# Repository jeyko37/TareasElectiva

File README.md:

# Tareas Diseño Mecatronico
Mi pecadora - Omega

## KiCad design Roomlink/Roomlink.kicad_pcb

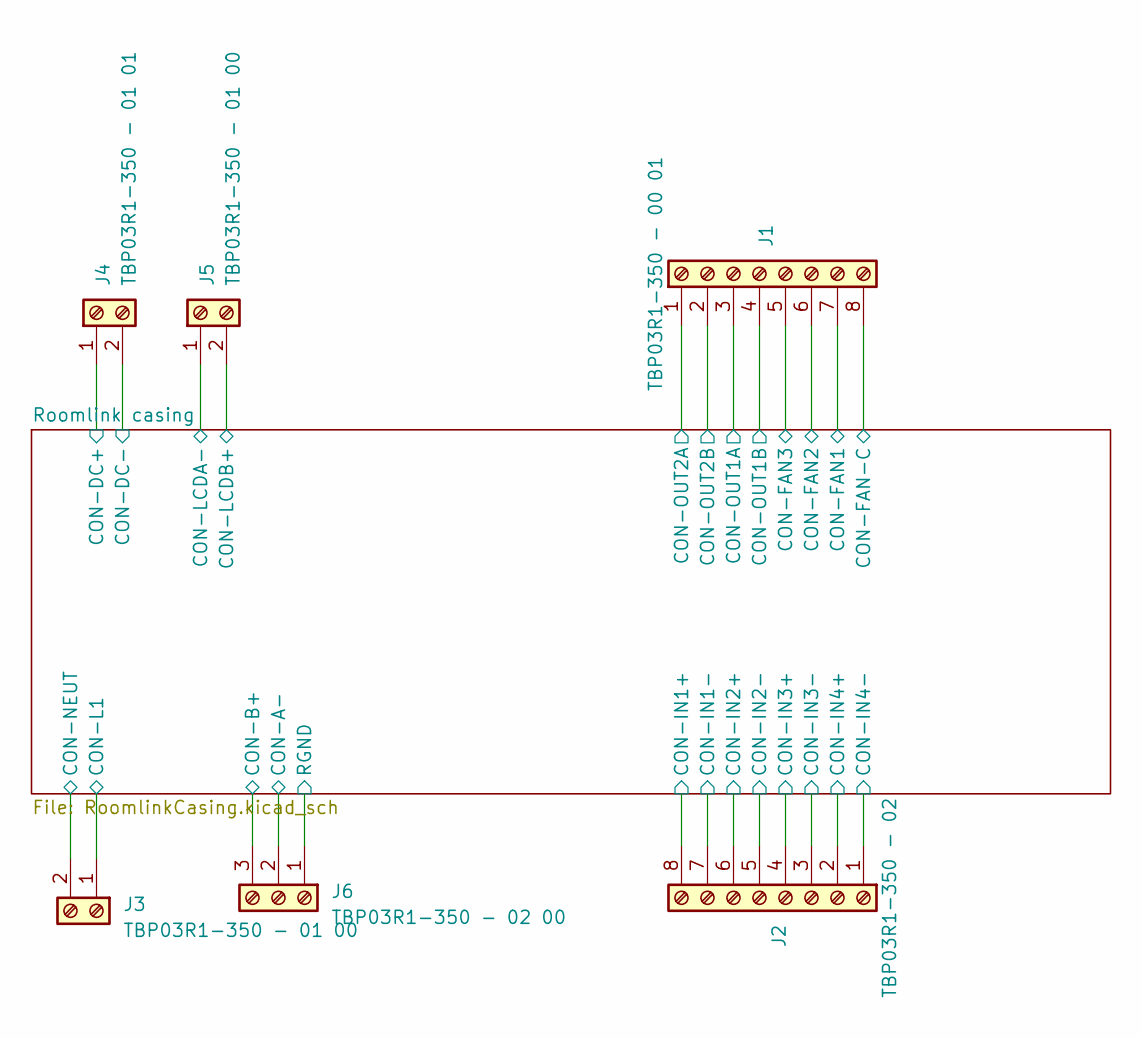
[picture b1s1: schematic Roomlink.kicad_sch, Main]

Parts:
J1: Screw_Terminal_01x08; CUI_TBP03R1-350-08GR; Part No. TBP03R1-350 - 00 01
J2: Screw_Terminal_01x08; CUI_TBP03R1-350-08GR; Part No. TBP03R1-350 - 02
J3, J5: TBP03R1-350 - 01 00; CUI_TBP03R1-350-02GR
J4: TBP03R1-350 - 01 01; CUI_TBP03R1-350-02GR
J6: TBP03R1-350 - 02 00; CUI_TBP03R1-350-03GR

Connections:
/Roomlink casing/CON-B+: J6.3; also elsewhere on the board
/Roomlink casing/CON-FAN1: J1.7; also elsewhere on the board
/Roomlink casing/CON-FAN2: J1.6; also elsewhere on the board
/Roomlink casing/CON-FAN3: J1.5; also elsewhere on the board
/Roomlink casing/CON-FAN-C: J1.8; also elsewhere on the board
/Roomlink casing/CON-IN1+: J2.8; also elsewhere on the board
/Roomlink casing/CON-IN1-: J2.7; also elsewhere on the board
/Roomlink casing/CON-IN2+: J2.6; also elsewhere on the board
/Roomlink casing/CON-IN2-: J2.5; also elsewhere on the board
/Roomlink casing/CON-IN3+: J2.4; also elsewhere on the board
/Roomlink casing/CON-IN3-: J2.3; also elsewhere on the board
/Roomlink casing/CON-IN4+: J2.2; also elsewhere on the board
/Roomlink casing/CON-IN4-: J2.1; also elsewhere on the board
/Roomlink casing/CON-L1: J3.1; also elsewhere on the board
/Roomlink casing/CON-LCDA-: J5.1; also elsewhere on the board
/Roomlink casing/CON-LCDB+: J5.2; also elsewhere on the board
/Roomlink casing/CON-NEUT: J3.2; also elsewhere on the board
/Roomlink casing/CON-OUT1A: J1.3; also elsewhere on the board
/Roomlink casing/CON-OUT1B: J1.4; also elsewhere on the board
/Roomlink casing/CON-OUT2A: J1.1; also elsewhere on the board
/Roomlink casing/CON-OUT2B: J1.2; also elsewhere on the board
/Roomlink casing/RGND: J6.1; also elsewhere on the board

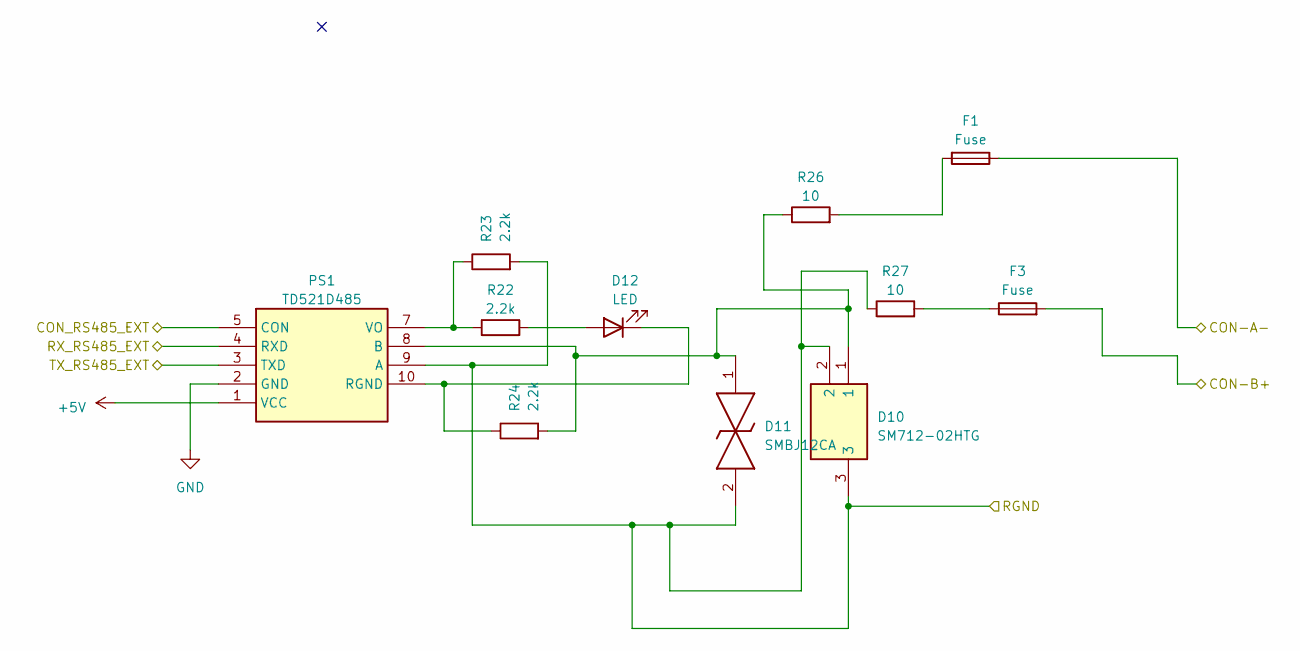
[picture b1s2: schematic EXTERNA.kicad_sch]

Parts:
D10: SM712-02HTG; SM71202HTG; Manufacturer_Part_Number SM712-02HTG; Mouser Part Number 576-SM712-02HTG
D11: SMBJ12CA; DIONM5436X245N; Manufacturer_Part_Number SMBJ12CA; Mouser Part Number 821-SMBJ12CA
D12: LED; LED_0805_2012Metric_Pad1.15x1.40mm_HandSolder
F1, F3: Fuse; Fuse_0805_2012Metric
PS1: TD521D485; Manufacturer_Part_Number TD521D485
R22, R23, R24: 2.2k; R_0805_2012Metric_Pad1.20x1.40mm_HandSolder
R26, R27: 10; R_0805_2012Metric_Pad1.20x1.40mm_HandSolder

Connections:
+5V: PS1.1 (VCC); also elsewhere on the board
/Roomlink casing/CON-B+: F3.2; also elsewhere on the board
/Roomlink casing/CONTROL/CON_RS485_EXT: PS1.5 (CON); also elsewhere on the board
/Roomlink casing/CONTROL/RX_RS485_EXT: PS1.4 (RXD); also elsewhere on the board
/Roomlink casing/CONTROL/TX_RS485_EXT: PS1.3 (TXD); also elsewhere on the board
/Roomlink casing/RGND: D10.2, D10.3, D11.2, PS1.9 (A), R23.2, R27.1; also elsewhere on the board
unnamed: D12.2 (A), R22.2
unnamed: D12.1 (K), PS1.10 (RGND), R24.1
unnamed: F3.1, R27.2
unnamed: D10.1, D11.1, PS1.8 (B), R24.2, R26.1
unnamed: PS1.7 (VO), R22.1, R23.1

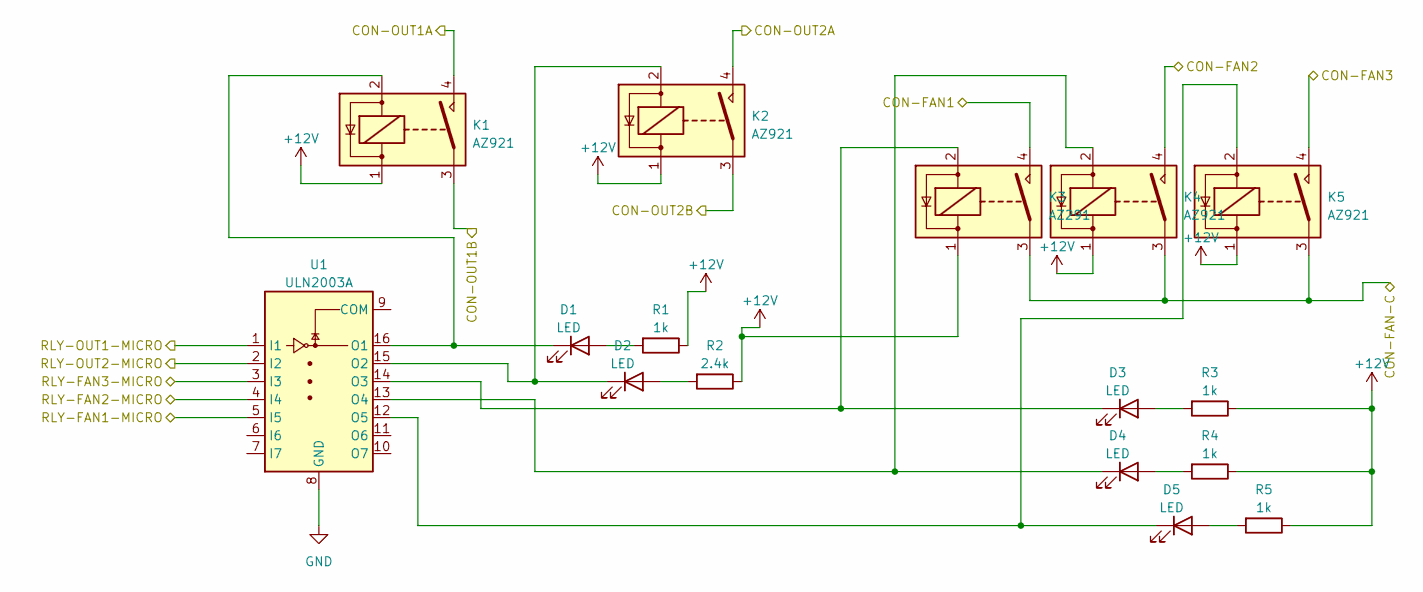
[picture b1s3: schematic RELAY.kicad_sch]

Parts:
D1, D2, D3, D4, D5: LED; LED_0805_2012Metric_Pad1.15x1.40mm_HandSolder
K1, K2, K4, K5: AZ921
K3: AZ291; AZ921
R1, R3, R4, R5: 1k; R_0805_2012Metric_Pad1.20x1.40mm_HandSolder
R2: 2.4k; R_0805_2012Metric_Pad1.20x1.40mm_HandSolder
U1: ULN2003A; DIP762W55P254L1940H508Q16N

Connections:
/Roomlink casing/CON-FAN1: K3.4; also elsewhere on the board
/Roomlink casing/CON-FAN2: K4.4; also elsewhere on the board
/Roomlink casing/CON-FAN3: K5.4; also elsewhere on the board
/Roomlink casing/CON-FAN-C: K3.3, K4.3, K5.3; also elsewhere on the board
/Roomlink casing/CON-OUT1A: K1.4; also elsewhere on the board
/Roomlink casing/CON-OUT1B: K1.3; also elsewhere on the board
/Roomlink casing/CON-OUT2A: K2.4; also elsewhere on the board
/Roomlink casing/CON-OUT2B: K2.3; also elsewhere on the board
/Roomlink casing/CONTROL/RLY-FAN1-MICRO: U1.5 (I5); also elsewhere on the board
/Roomlink casing/CONTROL/RLY-FAN2-MICRO: U1.4 (I4); also elsewhere on the board
/Roomlink casing/CONTROL/RLY-FAN3-MICRO: U1.3 (I3); also elsewhere on the board
/Roomlink casing/CONTROL/RLY-OUT1-MICRO: U1.1 (I1); also elsewhere on the board
/Roomlink casing/CONTROL/RLY-OUT2-MICRO: U1.2 (I2); also elsewhere on the board
unnamed: D1.2 (A), R1.2
unnamed: D1.1 (K), K1.2, U1.16 (O1)
unnamed: D2.2 (A), R2.2
unnamed: D2.1 (K), K2.2, U1.15 (O2)
unnamed: D3.2 (A), R3.2
unnamed: D3.1 (K), K3.2, U1.14 (O3)
unnamed: D4.2 (A), R4.2
unnamed: D4.1 (K), K4.2, U1.13 (O4)
unnamed: D5.2 (A), R5.2
unnamed: D5.1 (K), K5.2, U1.12 (O5)

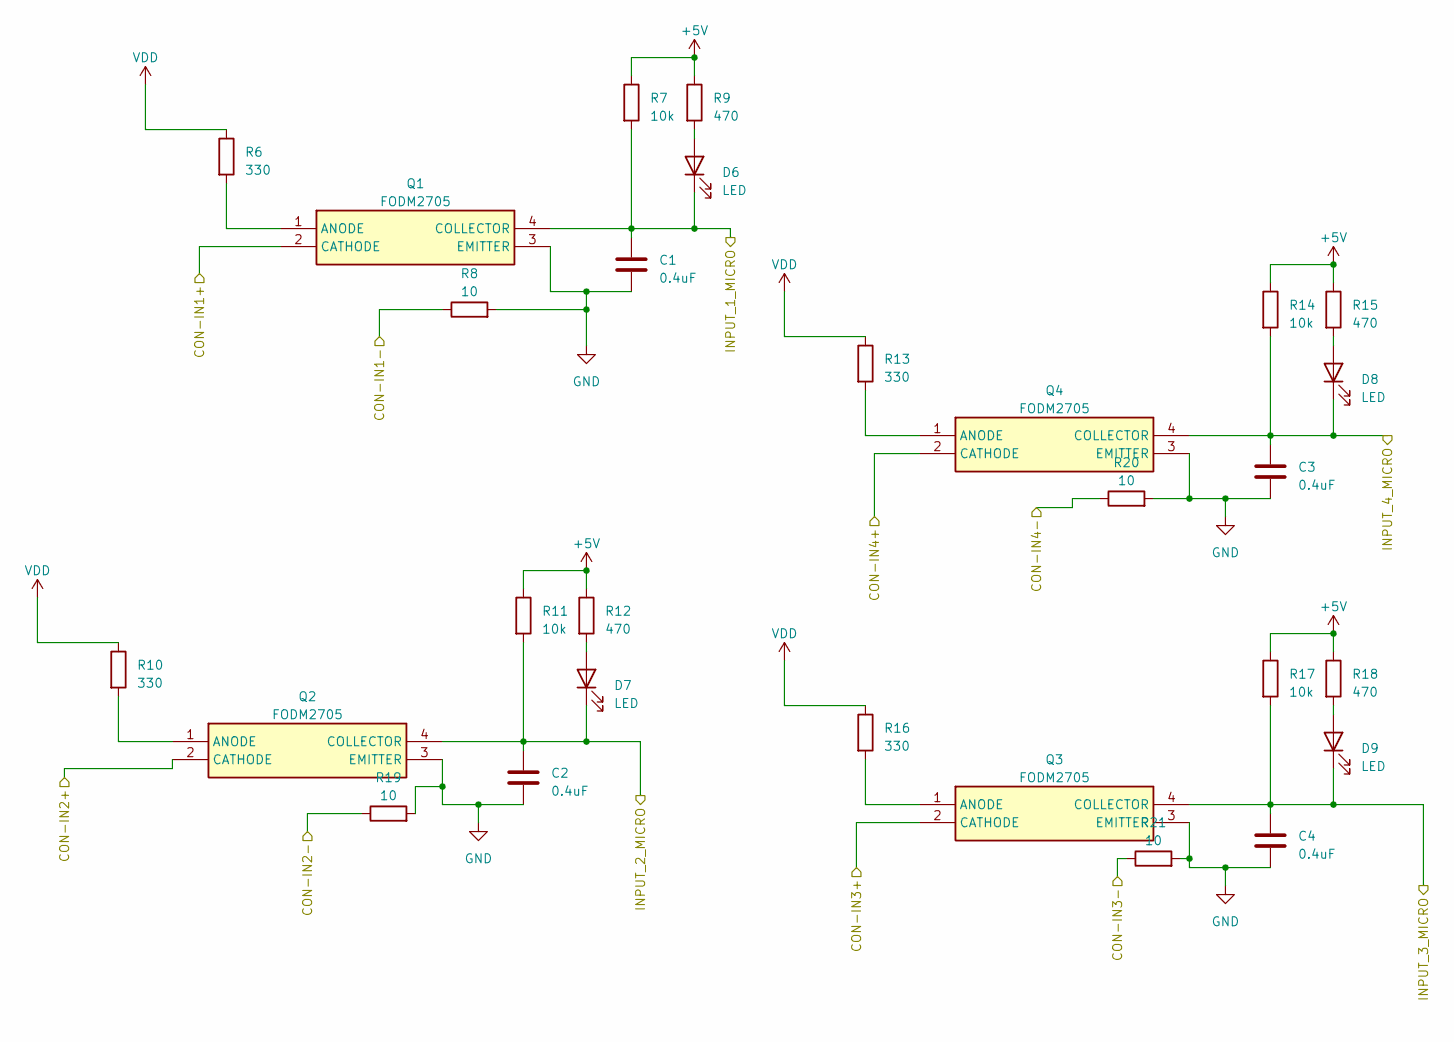
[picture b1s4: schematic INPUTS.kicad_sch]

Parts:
C1, C2, C3, C4: 0.4uF; C_0805_2012Metric_Pad1.18x1.45mm_HandSolder
D6, D7, D8, D9: LED; LED_0805_2012Metric_Pad1.15x1.40mm_HandSolder
Q1, Q2, Q3, Q4: FODM2705; SOP254P675X240-4N; Mouser Part Number 512-FODM2705
R6, R10, R13, R16: 330; R_0805_2012Metric_Pad1.20x1.40mm_HandSolder
R7, R11, R14, R17: 10k; R_0805_2012Metric_Pad1.20x1.40mm_HandSolder
R8, R19, R20, R21: 10; R_0805_2012Metric_Pad1.20x1.40mm_HandSolder
R9, R12, R15, R18: 470; R_0805_2012Metric_Pad1.20x1.40mm_HandSolder

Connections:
+5V: R7.1, R9.1, R11.1, R12.1, R14.1, R15.1, R17.1, R18.1; also elsewhere on the board
/Roomlink casing/CON-IN1+: Q1.2 (CATHODE); also elsewhere on the board
/Roomlink casing/CON-IN1-: R8.1; also elsewhere on the board
/Roomlink casing/CON-IN2+: Q2.2 (CATHODE); also elsewhere on the board
/Roomlink casing/CON-IN2-: R19.1; also elsewhere on the board
/Roomlink casing/CON-IN3+: Q3.2 (CATHODE); also elsewhere on the board
/Roomlink casing/CON-IN3-: R21.1; also elsewhere on the board
/Roomlink casing/CON-IN4+: Q4.2 (CATHODE); also elsewhere on the board
/Roomlink casing/CON-IN4-: R20.1; also elsewhere on the board
/Roomlink casing/CONTROL/INPUT_1_MICRO: C1.1, D6.1 (K), Q1.4 (COLLECTOR), R7.2; also elsewhere on the board
/Roomlink casing/CONTROL/INPUT_2_MICRO: C2.1, D7.1 (K), Q2.4 (COLLECTOR), R11.2; also elsewhere on the board
/Roomlink casing/CONTROL/INPUT_3_MICRO: C4.1, D9.1 (K), Q3.4 (COLLECTOR), R17.2; also elsewhere on the board
/Roomlink casing/CONTROL/INPUT_4_MICRO: C3.1, D8.1 (K), Q4.4 (COLLECTOR), R14.2; also elsewhere on the board
unnamed: D6.2 (A), R9.2
unnamed: D7.2 (A), R12.2
unnamed: D8.2 (A), R15.2
unnamed: D9.2 (A), R18.2
unnamed: Q1.1 (ANODE), R6.2
unnamed: Q2.1 (ANODE), R10.2
unnamed: Q3.1 (ANODE), R16.2
unnamed: Q4.1 (ANODE), R13.2
VDD: R6.1, R10.1, R13.1, R16.1; also elsewhere on the board

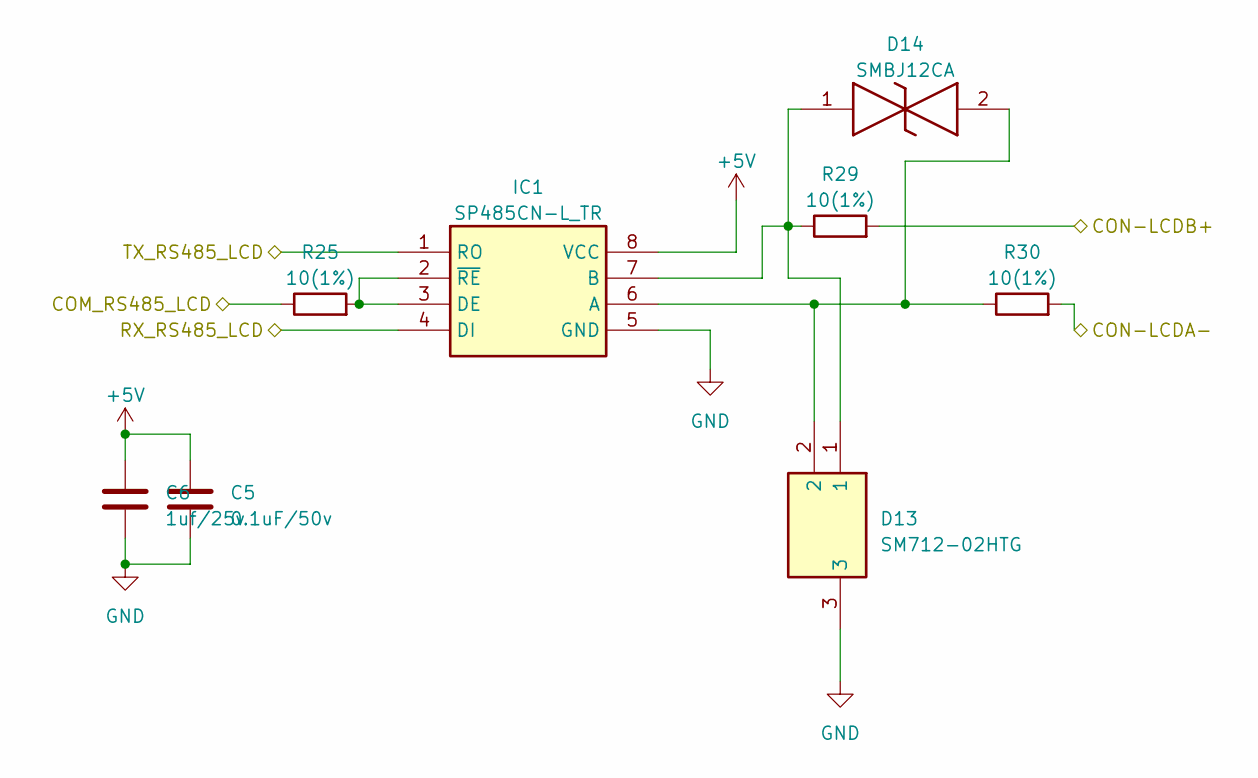
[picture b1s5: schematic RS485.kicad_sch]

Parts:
C5: 0.1uF/50v; C_0805_2012Metric_Pad1.18x1.45mm_HandSolder
C6: 1uf/25v; C_0805_2012Metric_Pad1.18x1.45mm_HandSolder
D13: SM712-02HTG; SM71202HTG; Manufacturer_Part_Number SM712-02HTG; Mouser Part Number 576-SM712-02HTG
D14: SMBJ12CA; DIONM5436X245N; Manufacturer_Part_Number SMBJ12CA; Mouser Part Number 821-SMBJ12CA
IC1: SP485CN-L_TR; SOIC127P600X175-8N; Manufacturer_Part_Number SP485CN-L/TR; Mouser Part Number 701-SP485CN-L/TR
R25, R29, R30: 10(1%); R_0805_2012Metric_Pad1.20x1.40mm_HandSolder

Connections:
+5V: C5.1, C6.1, IC1.8 (VCC); also elsewhere on the board
/Roomlink casing/CON-LCDA-: R30.2; also elsewhere on the board
/Roomlink casing/CON-LCDB+: R29.2; also elsewhere on the board
/Roomlink casing/CONTROL/COM_RS485_LCD: R25.1; also elsewhere on the board
/Roomlink casing/CONTROL/RX_RS485_LCD: IC1.4 (DI); also elsewhere on the board
/Roomlink casing/CONTROL/TX_RS485_LCD: IC1.1 (RO); also elsewhere on the board
unnamed: D13.2, D14.2, IC1.6 (A), R30.1
unnamed: D13.1, D14.1, IC1.7 (B), R29.1
unnamed: IC1.2 (~RE), IC1.3 (DE), R25.2

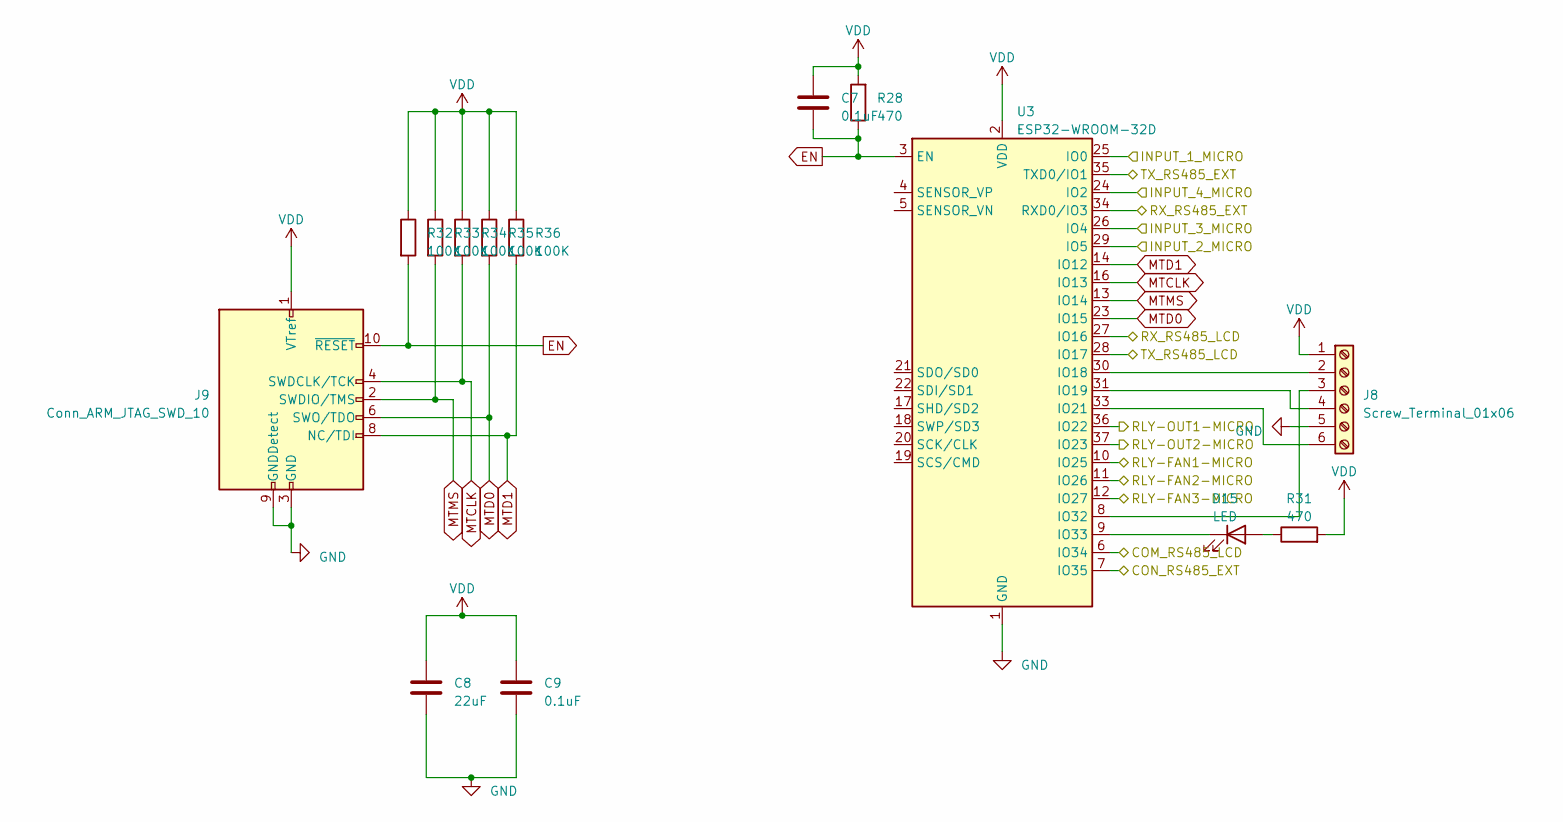
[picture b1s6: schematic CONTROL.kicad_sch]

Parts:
C7, C9: 0.1uF; C_0805_2012Metric_Pad1.18x1.45mm_HandSolder
C8: 22uF; C_0805_2012Metric_Pad1.18x1.45mm_HandSolder
D15: LED; LED_0805_2012Metric_Pad1.15x1.40mm_HandSolder
J8: Screw_Terminal_01x06; PinHeader_2x03_P2.54mm_Vertical
J9: Conn_ARM_JTAG_SWD_10; PinHeader_2x05_P2.54mm_Vertical
R28, R31: 470; R_0805_2012Metric_Pad1.20x1.40mm_HandSolder
R32, R33, R34, R35, R36: 100K; R_0805_2012Metric_Pad1.20x1.40mm_HandSolder
U3: ESP32-WROOM-32D

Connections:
/Roomlink casing/CONTROL/COM_RS485_LCD: U3.6 (IO34); also elsewhere on the board
/Roomlink casing/CONTROL/CON_RS485_EXT: U3.7 (IO35); also elsewhere on the board
/Roomlink casing/CONTROL/INPUT_1_MICRO: U3.25 (IO0); also elsewhere on the board
/Roomlink casing/CONTROL/INPUT_2_MICRO: U3.29 (IO5); also elsewhere on the board
/Roomlink casing/CONTROL/INPUT_3_MICRO: U3.26 (IO4); also elsewhere on the board
/Roomlink casing/CONTROL/INPUT_4_MICRO: U3.24 (IO2); also elsewhere on the board
/Roomlink casing/CONTROL/RLY-FAN1-MICRO: U3.10 (IO25); also elsewhere on the board
/Roomlink casing/CONTROL/RLY-FAN2-MICRO: U3.11 (IO26); also elsewhere on the board
/Roomlink casing/CONTROL/RLY-FAN3-MICRO: U3.12 (IO27); also elsewhere on the board
/Roomlink casing/CONTROL/RLY-OUT1-MICRO: U3.36 (IO22); also elsewhere on the board
/Roomlink casing/CONTROL/RLY-OUT2-MICRO: U3.37 (IO23); also elsewhere on the board
/Roomlink casing/CONTROL/RX_RS485_EXT: U3.34 (RXD0/IO3); also elsewhere on the board
/Roomlink casing/CONTROL/RX_RS485_LCD: U3.27 (IO16); also elsewhere on the board
/Roomlink casing/CONTROL/TX_RS485_EXT: U3.35 (TXD0/IO1); also elsewhere on the board
/Roomlink casing/CONTROL/TX_RS485_LCD: U3.28 (IO17); also elsewhere on the board
EN: C7.2, J9.10 (~RESET), R28.1, R32.2, U3.3 (EN)
MTCLK: J9.4 (SWDCLK/TCK), R34.2, U3.16 (IO13)
MTD0: J9.6 (SWO/TDO), R35.2, U3.23 (IO15)
MTD1: J9.8 (NC/TDI), R36.2, U3.14 (IO12)
MTMS: J9.2 (SWDIO/TMS), R33.2, U3.13 (IO14)
unnamed: D15.2 (A), R31.1
unnamed: D15.1 (K), U3.9 (IO33)
unnamed: J8.2, U3.30 (IO18)
unnamed: J8.3, U3.8 (IO32)
unnamed: J8.4, U3.31 (IO19)
unnamed: J8.6, U3.33 (IO21)
VDD: C7.1, C8.1, C9.1, J8.1, J9.1 (VTref), R28.2, R31.2, R32.1, R33.1, R34.1, R35.1, R36.1, U3.2 (VDD); also elsewhere on the board

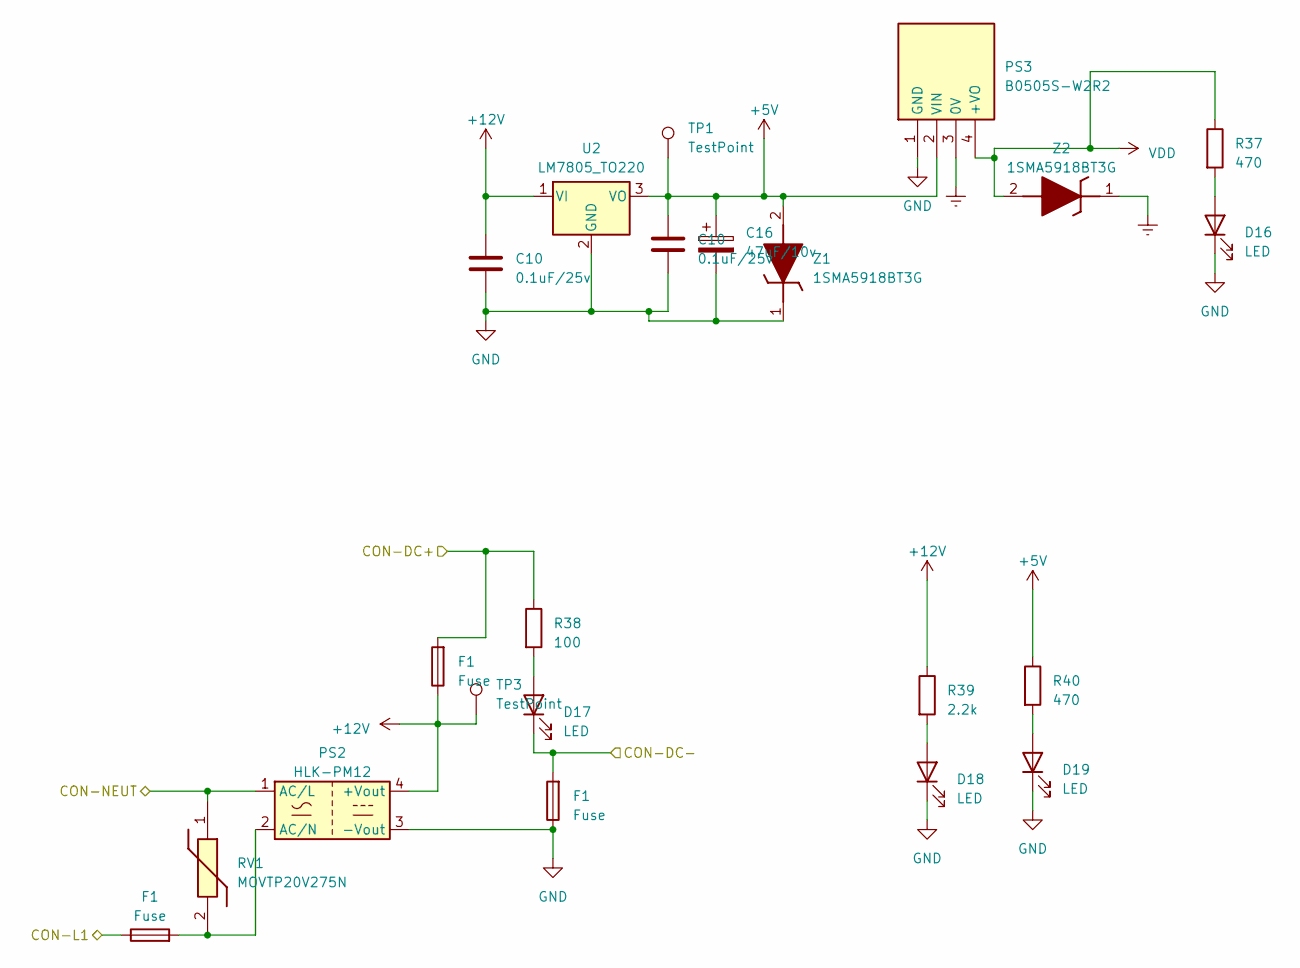
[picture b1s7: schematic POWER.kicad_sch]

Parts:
C10: 0.1uF/25v; C_0805_2012Metric_Pad1.18x1.45mm_HandSolder
C16: 47uF/10v; C_0805_2012Metric_Pad1.18x1.45mm_HandSolder
D16, D17, D18, D19: LED; LED_0805_2012Metric_Pad1.15x1.40mm_HandSolder
F1: Fuse; Fuse_0805_2012Metric
PS2: HLK-PM12; Converter_ACDC_HiLink_HLK-PMxx
PS3: B0505S-W2R2; B0505SW2R2; Manufacturer_Part_Number B0505S-W2R2
R37, R40: 470; R_0805_2012Metric_Pad1.20x1.40mm_HandSolder
R38: 100; R_0805_2012Metric_Pad1.20x1.40mm_HandSolder
R39: 2.2k; R_0805_2012Metric_Pad1.20x1.40mm_HandSolder
RV1: MOVTP20V275N; Manufacturer_Part_Number MOVTP20V275N
TP1, TP3: TestPoint; TestPoint_Pad_D1.5mm
U2: LM7805_TO220; TO-220-3_Vertical
Z1, Z2: 1SMA5918BT3G; DIOM5226X220N; Manufacturer_Part_Number 1SMA5918BT3G; Mouser Part Number 863-1SMA5918BT3G

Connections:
+5V: C16.1, PS3.2 (VIN), R40.1, TP1.1, U2.3 (VO), Z1.2 (A); also elsewhere on the board
/Roomlink casing/CON-NEUT: PS2.1 (AC/L), RV1.1; also elsewhere on the board
Earth: PS3.3 (0V), Z2.1 (K)
unnamed: D16.2 (A), R37.2
unnamed: D17.2 (A), R38.2
unnamed: D18.2 (A), R39.2
unnamed: D19.2 (A), R40.2
VDD: PS3.4 (+VO), R37.1, Z2.2 (A); also elsewhere on the board

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
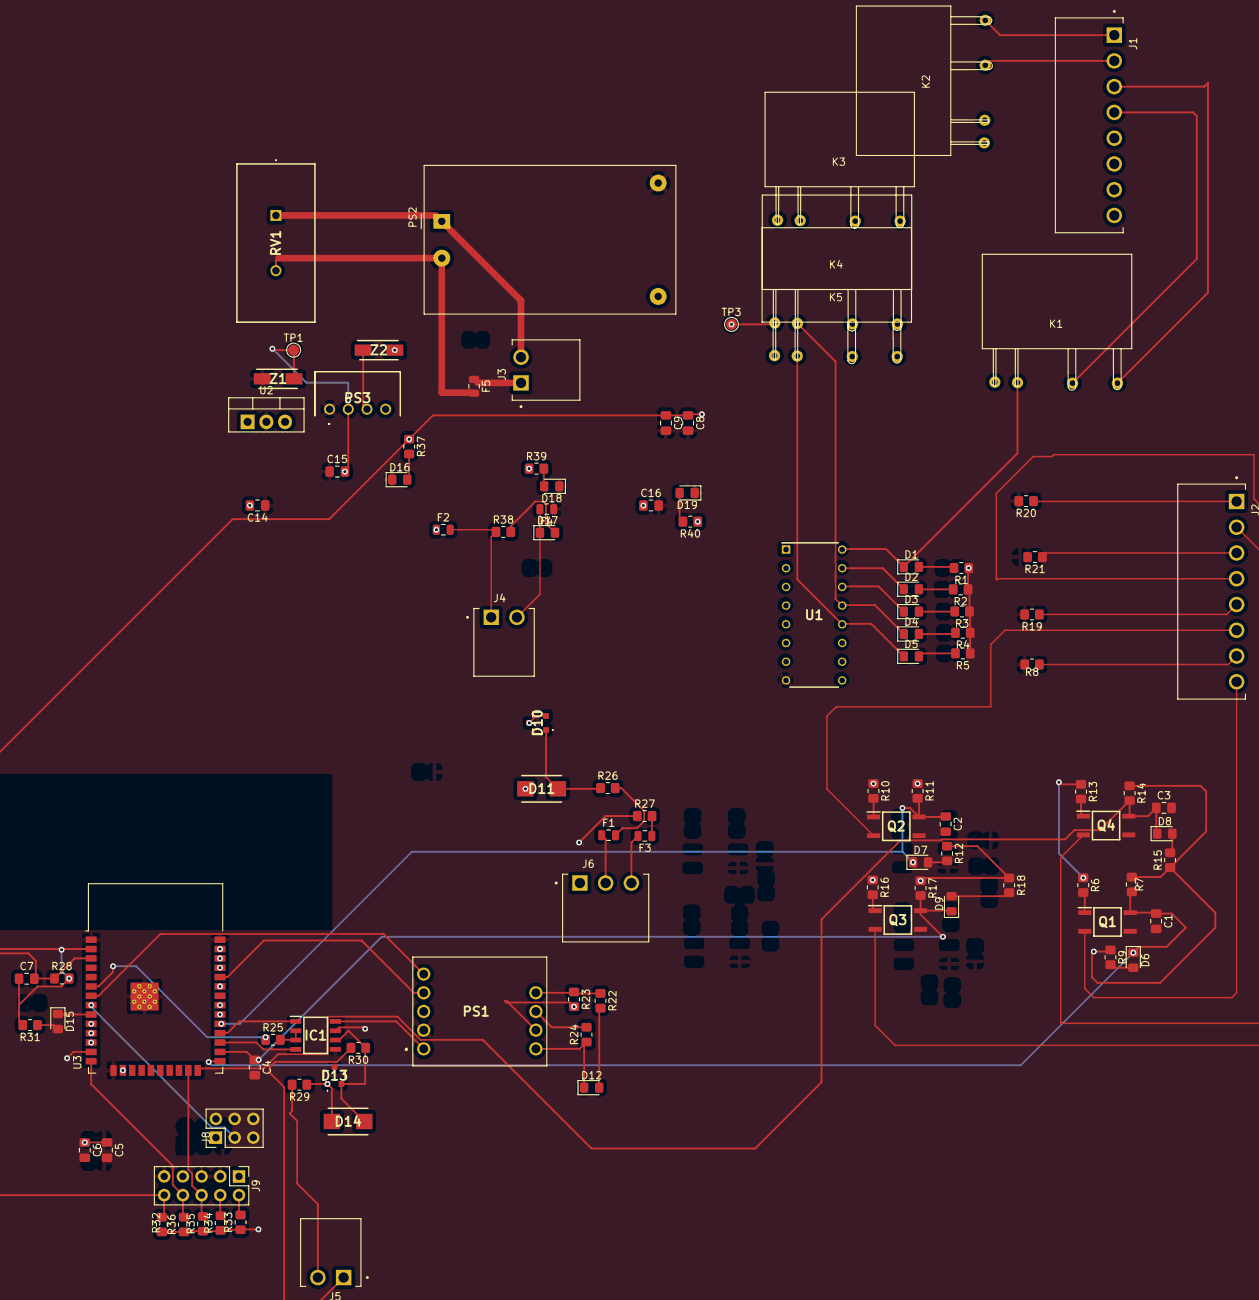
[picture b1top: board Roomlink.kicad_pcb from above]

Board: 8 copper layers, 105 parts (0 on the bottom side), 88 nets.

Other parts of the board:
C14, C15: 0.1uF/25v; C_0805_2012Metric_Pad1.18x1.45mm_HandSolder
F2, F4, F5: Fuse; Fuse_0805_2012Metric

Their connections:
+5V: C15.2; also elsewhere on the board
/Roomlink casing/CON-L1: F5.1; also elsewhere on the board

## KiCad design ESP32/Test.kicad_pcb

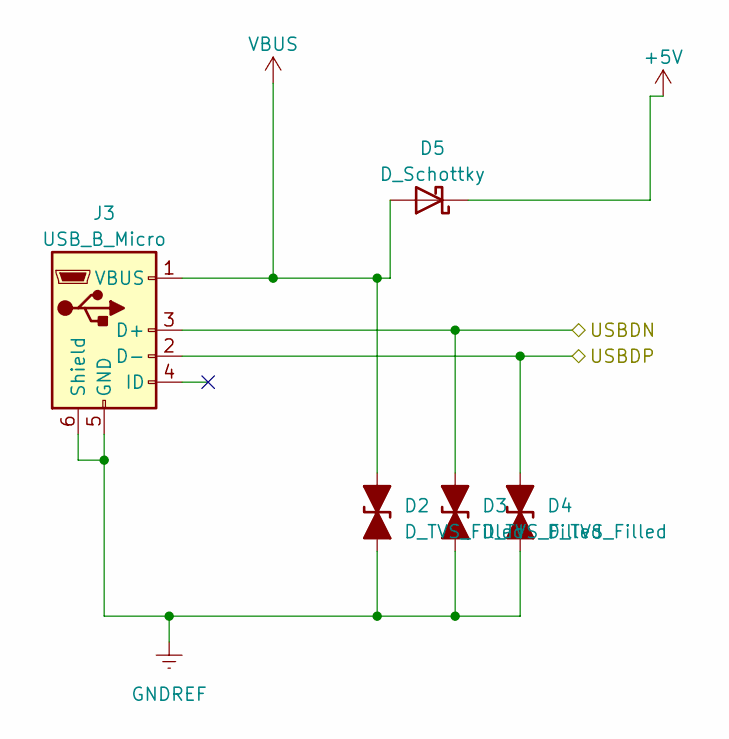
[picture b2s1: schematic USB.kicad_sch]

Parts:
D2, D3, D4: D_TVS_Filled; TVS_LESD5D5.0CT1G
D5: D_Schottky; D_SOD-323
J3: USB_B_Micro; USB_Micro-B_Molex-105017-0001

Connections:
+5V: D5.1 (K); also elsewhere on the board
/Micro_bus/USB_DN: D3.1 (A1), J3.3 (D+); also elsewhere on the board
/Micro_bus/USB_DP: D4.1 (A1), J3.2 (D-); also elsewhere on the board
GNDREF: D2.2 (A2), D3.2 (A2), D4.2 (A2), J3.5 (GND), J3.6 (Shield); also elsewhere on the board
VBUS: D2.1 (A1), D5.2 (A), J3.1 (VBUS); also elsewhere on the board

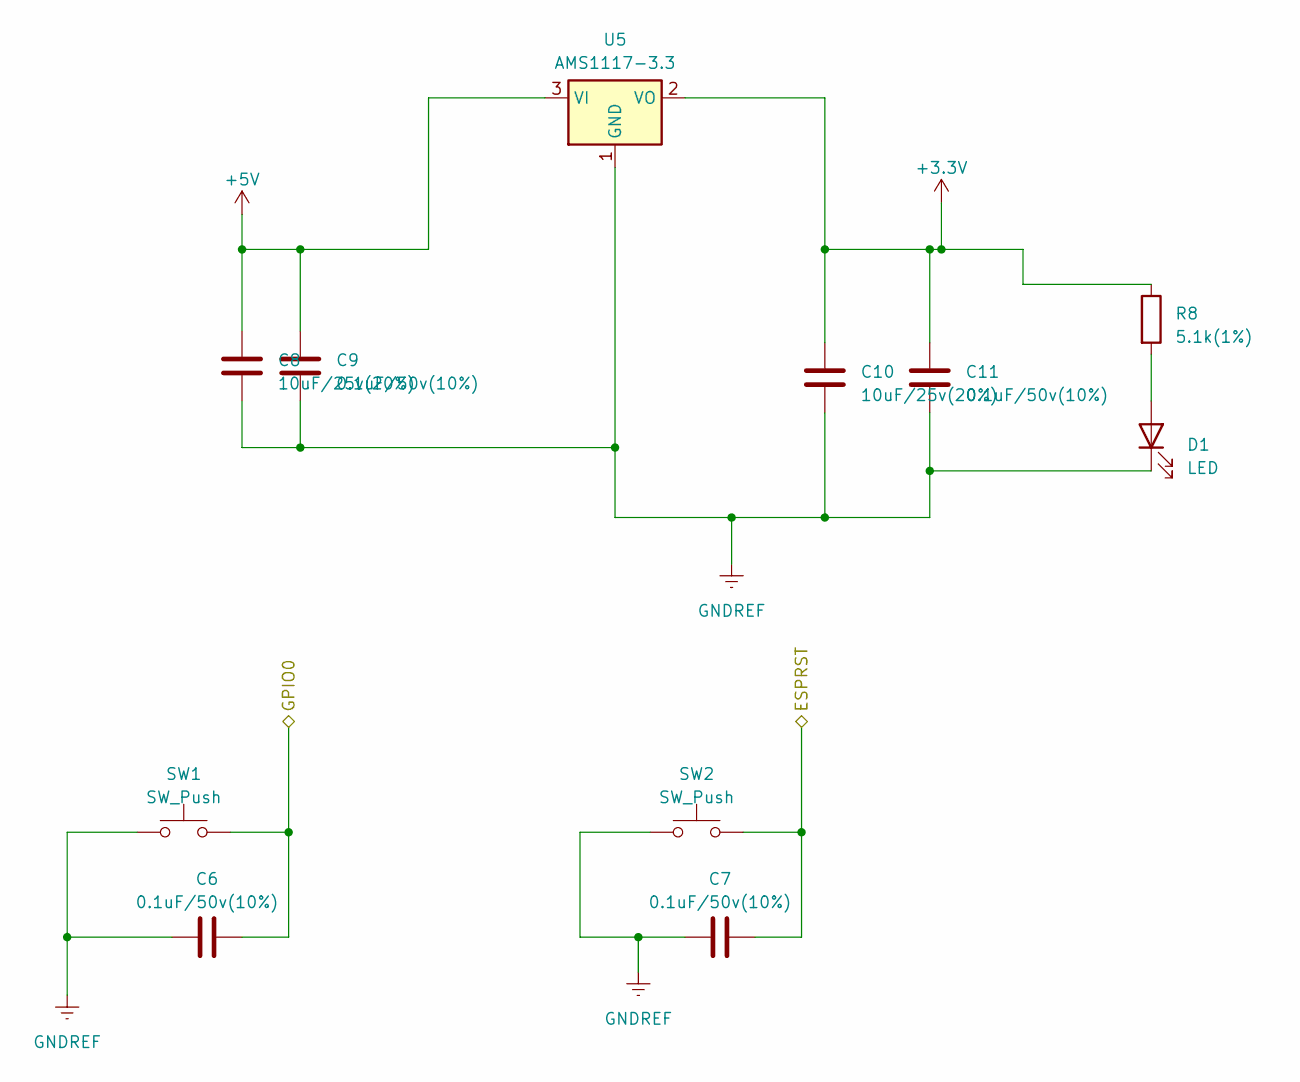
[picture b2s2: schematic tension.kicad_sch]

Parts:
C6, C7, C9, C11: 0.1uF/50v(10%); C_0603_1608Metric
C8, C10: 10uF/25v(20%); C_0603_1608Metric
D1: LED; LED_0805_2012Metric
R8: 5.1k(1%); R_0402_1005Metric_Pad0.72x0.64mm_HandSolder
SW1, SW2: SW_Push; SW_SPST_B3U-1000P
U5: AMS1117-3.3; SOT-223-3_TabPin2

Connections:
+3.3V: C10.2, C11.2, R8.1, U5.2 (VO); also elsewhere on the board
+5V: C8.2, C9.2, U5.3 (VI); also elsewhere on the board
ESPRST: C7.2, SW2.2; also elsewhere on the board
GNDREF: C6.1, C7.1, C8.1, C9.1, C10.1, C11.1, D1.1 (K), SW1.1, SW2.1, U5.1 (GND); also elsewhere on the board
IO0: C6.2, SW1.2; also elsewhere on the board
unnamed: D1.2 (A), R8.2

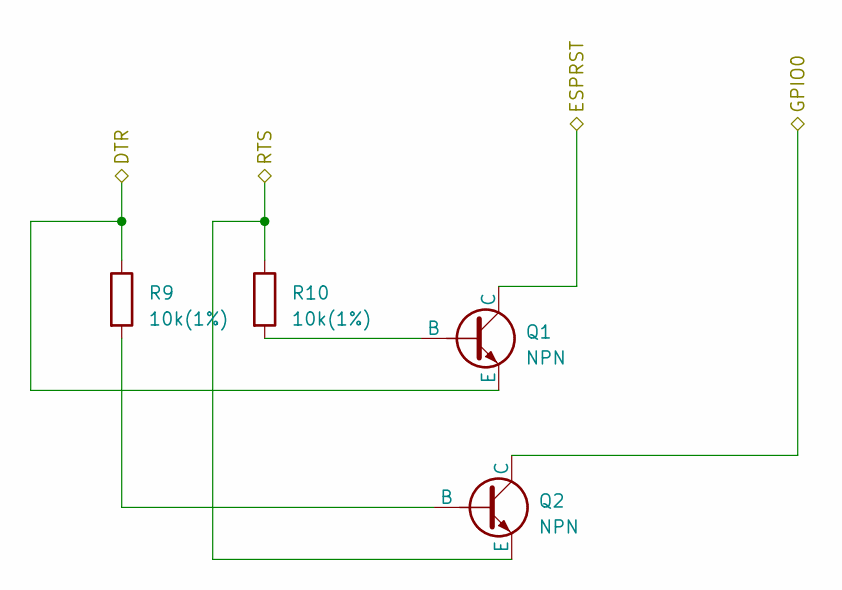
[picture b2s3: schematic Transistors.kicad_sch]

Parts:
Q1, Q2: NPN; TSOT-23
R9, R10: 10k(1%); R_0402_1005Metric_Pad0.72x0.64mm_HandSolder

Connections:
/Micro_bus/DTR: Q1.3 (E), R9.1; also elsewhere on the board
/Micro_bus/RTS: Q2.3 (E), R10.1; also elsewhere on the board
ESPRST: Q1.1 (C); also elsewhere on the board
IO0: Q2.1 (C); also elsewhere on the board
unnamed: Q1.2 (B), R10.2
unnamed: Q2.2 (B), R9.2

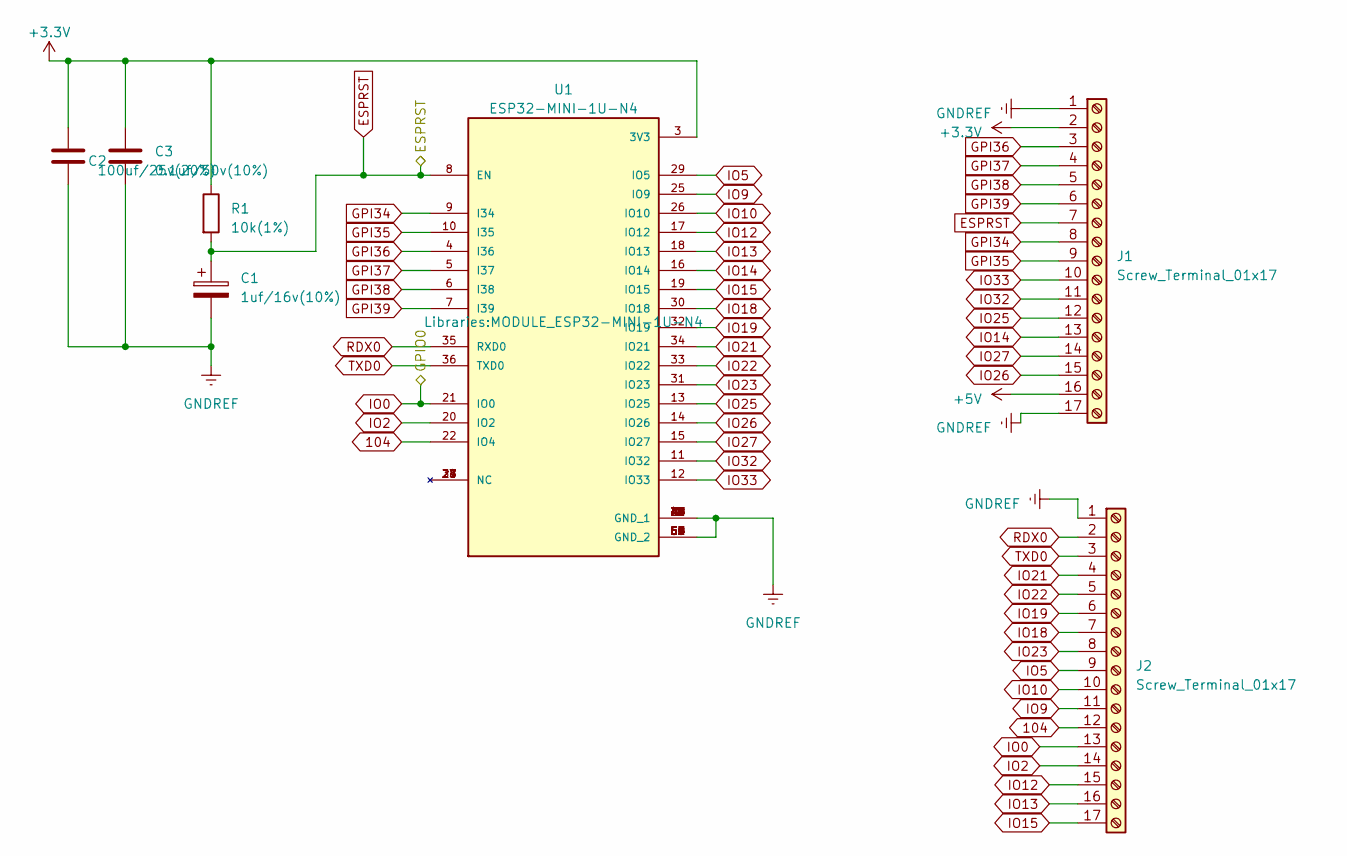
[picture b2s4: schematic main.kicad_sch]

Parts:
C1: 1uf/16v(10%); C_0603_1608Metric
C2: 100uf/25v(20%); C_0603_1608Metric
C3: 0.1uf/50v(10%); C_0603_1608Metric
J1, J2: Screw_Terminal_01x17; PinHeader_1x17_P2.54mm_Vertical
R1: 10k(1%); R_0402_1005Metric_Pad0.72x0.64mm_HandSolder
U1: ESP32-MINI-1U-N4; MODULE_ESP32-MINI-1U-N4; PARTREV v1.2

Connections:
104: J2.12, U1.22 (IO4)
+3.3V: C2.1, C3.1, J1.2, R1.1, U1.3 (3V3); also elsewhere on the board
+5V: J1.16; also elsewhere on the board
ESPRST: C1.1, J1.7, R1.2, U1.8 (EN); also elsewhere on the board
GNDREF: C1.2, C2.2, C3.2, J1.1, J1.17, J2.1, U1.1 (GND_1), U1.2 (GND_1), U1.27 (GND_1), U1.38 (GND_1), U1.39 (GND_1), U1.40 (GND_1), U1.41 (GND_1), U1.42 (GND_1), U1.43 (GND_1), U1.44 (GND_1), U1.45 (GND_1), U1.46 (GND_1), U1.47 (GND_1), U1.48 (GND_1), U1.49 (GND_1), U1.50 (GND_2), U1.51 (GND_2), U1.52 (GND_2), U1.53 (GND_2), U1.54 (GND_2), U1.55 (GND_2), U1.56 (GND_2), U1.57 (GND_2), U1.58 (GND_2), U1.59 (GND_2), U1.60 (GND_2), U1.61 (GND_2), U1.62 (GND_2); also elsewhere on the board
GPI34: J1.8, U1.9 (I34)
GPI35: J1.9, U1.10 (I35)
GPI36: J1.3, U1.4 (I36)
GPI37: J1.4, U1.5 (I37)
GPI38: J1.5, U1.6 (I38)
GPI39: J1.6, U1.7 (I39)
IO0: J2.13, U1.21 (IO0); also elsewhere on the board
IO2: J2.14, U1.20 (IO2)
IO5: J2.9, U1.29 (IO5)
IO9: J2.11, U1.25 (IO9)
IO10: J2.10, U1.26 (IO10)
IO12: J2.15, U1.17 (IO12)
IO13: J2.16, U1.18 (IO13)
IO14: J1.13, U1.16 (IO14)
IO15: J2.17, U1.19 (IO15)
IO18: J2.7, U1.30 (IO18)
IO19: J2.6, U1.32 (IO19)
IO21: J2.4, U1.34 (IO21)
IO22: J2.5, U1.33 (IO22)
IO23: J2.8, U1.31 (IO23)
IO25: J1.12, U1.13 (IO25)
IO26: J1.15, U1.14 (IO26)
IO27: J1.14, U1.15 (IO27)
IO32: J1.11, U1.11 (IO32)
IO33: J1.10, U1.12 (IO33)
RDX0: J2.2, U1.35 (RXD0)
TXD0: J2.3, U1.36 (TXD0)
